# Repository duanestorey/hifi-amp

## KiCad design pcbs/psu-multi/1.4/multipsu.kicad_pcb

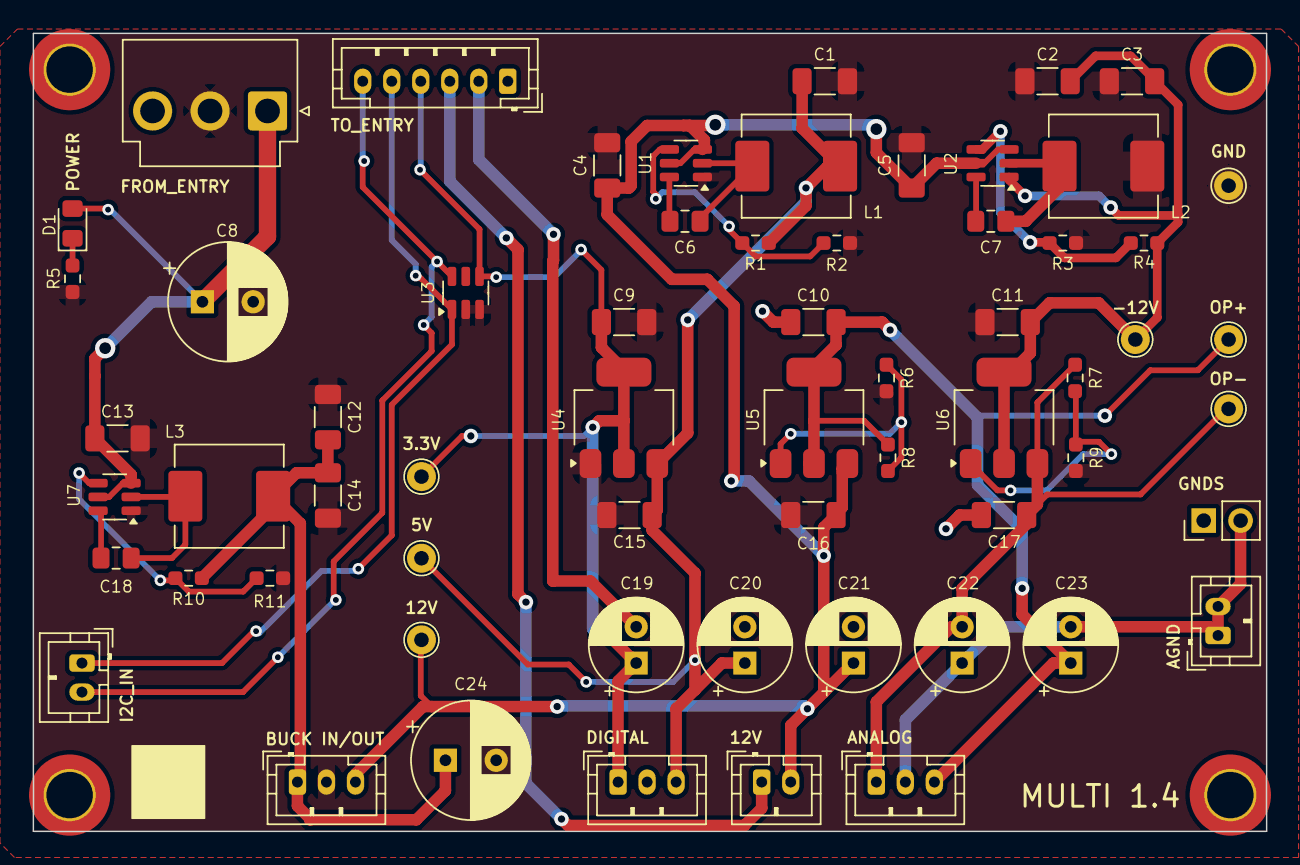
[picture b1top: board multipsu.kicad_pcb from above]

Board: 2 copper layers, 85.0 x 55.0 mm, 66 parts (0 on the bottom side), 27 nets.

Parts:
C1, C2, C3, C12, C14: 22U 25V; C_1206_3216Metric_Pad1.33x1.80mm_HandSolder
C4, C5, C13: 10U 50V; C_1206_3216Metric_Pad1.33x1.80mm_HandSolder
C6, C7, C18: 0.1u; C_0805_2012Metric_Pad1.18x1.45mm_HandSolder
C8: 100u 50V; CP_Radial_D8.0mm_P3.50mm
C9, C10, C15, C17: 10U; C_1206_3216Metric_Pad1.33x1.80mm_HandSolder
C11, C16: 10u; C_1206_3216Metric_Pad1.33x1.80mm_HandSolder
C19, C20, C21, C22, C23: 220u 16V; CP_Radial_D6.3mm_P2.50mm
C24: 1000u 16V; CP_Radial_D8.0mm_P3.50mm
D1: BLUE; LED_0805_2012Metric_Pad1.15x1.40mm_HandSolder
H1, H2, H3, H4: MountingHole; MountingHole_3.2mm_M3_DIN965_Pad_TopOnly
J1: Conn_01x06_Pin; JST_PH_B6B-PH-K_1x06_P2.00mm_Vertical
J2: Conn_01x03_Male; JST_VH_B3P-VH_1x03_P3.96mm_Vertical
J3: Conn_01x02; PinHeader_1x02_P2.54mm_Vertical
J4, J5, J8: Conn_01x02_Pin; JST_PH_B2B-PH-K_1x02_P2.00mm_Vertical
J6, J7, J9: Conn_01x03_Pin; JST_PH_B3B-PH-K_1x03_P2.00mm_Vertical
L1: 3.3u; L_Sunlord_MWSA0605S
L2, L3: 6.8u; L_Sunlord_MWSA0605S
R1, R3, R10: 100K; R_0603_1608Metric_Pad0.98x0.95mm_HandSolder
R2: 13.7K; R_0603_1608Metric_Pad0.98x0.95mm_HandSolder
R4, R11: 5.23K; R_0603_1608Metric_Pad0.98x0.95mm_HandSolder
R5: 16K; R_0603_1608Metric_Pad0.98x0.95mm_HandSolder
R6, R9: 1.6K; R_0603_1608Metric_Pad0.98x0.95mm_HandSolder
R7, R8: 240R; R_0603_1608Metric_Pad0.98x0.95mm_HandSolder
TP1, TP2, TP3, TP4, TP5, TP6, TP7: TestPoint; TestPoint_THTPad_D2.0mm_Drill1.0mm
U1, U2, U7: LMR51430; SOT-23-6
U3: TMP100; SOT-23-6
U4: ZLDO1117QG33TA; SOT-223-3_TabPin2
U5: LM317_SOT-223; SOT-223-3_TabPin2
U6: LM337_SOT223; SOT-223-3_TabPin2

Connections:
3V3: C9.1, C19.1, J1.4, J7.1, TP5.1, U3.4 (V+), U4.2 (VO)
5V: C1.1, C15.1, C20.1, J7.3, L1.2, R1.1, TP6.1, U4.3 (VI)
12V: C4.1, C5.1, C16.1, C21.1, J6.3, J8.2, TP7.1, U1.3 (VIN), U1.5 (EN), U2.3 (VIN), U2.5 (EN), U5.3 (VI)
12V_OUT: C12.1, C14.1, C24.1, J6.1, L3.2, R10.1
-12V: C2.2, C3.2, C11.2, R4.2, TP2.1, U2.1 (GND), U6.2 (VI)
AGND: C10.2, C17.1, J1.1, J3.1
AGND_INT: C22.1, C23.2, J3.2, J4.1, J4.2, J9.2
DC_NEG: C17.2, C22.2, J9.1, R7.1, TP4.1, U6.3 (VO)
DC_POS: C10.1, C23.1, J9.3, R8.1, TP3.1, U5.2 (VO)
GND: C19.2, C20.2, C21.2, J1.2, J7.2
unnamed: D1.1 (K), R5.1
unnamed: C6.1, U1.6 (CB)
unnamed: R1.2, R2.1, U1.4 (FB)
unnamed: C6.2, L1.1, U1.2 (SW)
unnamed: C7.1, U2.6 (CB)
unnamed: R3.2, R4.1, U2.4 (FB)
unnamed: C7.2, L2.1, U2.2 (SW)
unnamed: R6.1, R8.2, U5.1 (ADJ)
unnamed: R7.2, R9.1, U6.1 (ADJ)
unnamed: C18.1, U7.6 (CB)
unnamed: R10.2, R11.1, U7.4 (FB)
unnamed: C18.2, L3.1, U7.2 (SW)
PGND: C1.2, C2.1, C3.1, C4.2, C5.2, C8.2, C9.2, C11.1, C12.2, C13.2, C14.2, C15.2, C16.2, C24.2, J2.2, J6.2, L2.2, R2.2, R3.1, R5.2, R6.2, R9.2, R11.2, TP1.1, U1.1 (GND), U3.2 (GND), U3.3 (ADD1), U4.1 (GND), U7.1 (GND)
RELAY_GND: J1.3, J8.1
SCL: J1.5, J5.1, U3.1 (SCL)
SDA: J1.6, J5.2, U3.6 (SDA)
VP: C8.1, C13.1, D1.2 (A), J2.1, U7.3 (VIN), U7.5 (EN)

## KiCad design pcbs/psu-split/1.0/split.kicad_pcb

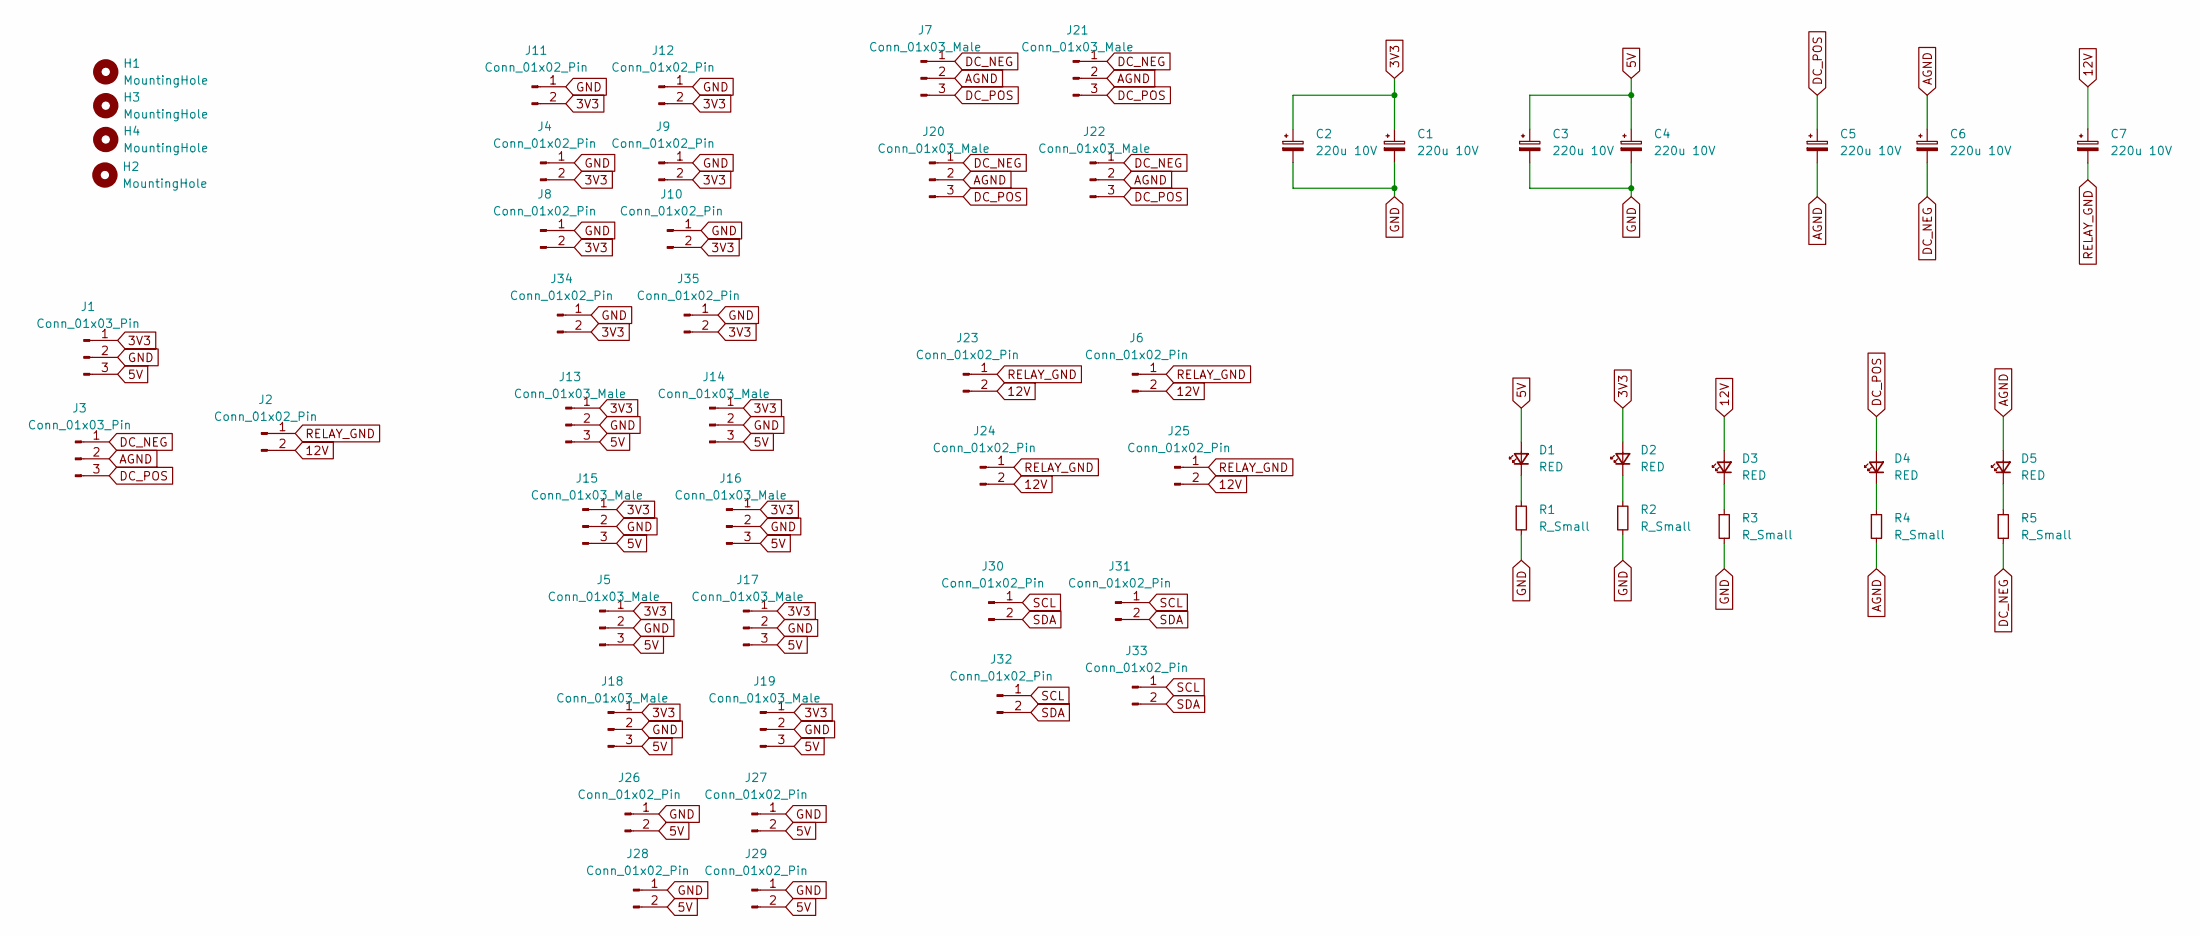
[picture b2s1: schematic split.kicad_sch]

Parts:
C1, C2, C3, C4, C5, C6: 220u 10V; CP_Radial_D10.0mm_P2.50mm_P5.00mm
C7: 220u 10V; CP_Radial_D6.3mm_P2.50mm
D1, D2, D3, D4, D5: RED; LED_0805_2012Metric_Pad1.15x1.40mm_HandSolder
H1, H2, H3, H4: MountingHole; MountingHole_3.2mm_M3_DIN965_Pad_TopOnly
J1, J3: Conn_01x03_Pin; JST_PH_B3B-PH-K_1x03_P2.00mm_Vertical
J2, J4, J6, J8, J9, J10, J11, J12, J23, J24, J25, J26, J27, J28, J29, J30, J31, J32, J33, J34, J35: Conn_01x02_Pin; JST_PH_B2B-PH-K_1x02_P2.00mm_Vertical
J5, J7, J13, J14, J15, J16, J17, J18, J19, J20, J21, J22: Conn_01x03_Male; JST_PH_B3B-PH-K_1x03_P2.00mm_Vertical
R1, R2, R3, R4, R5: R_Small; R_0603_1608Metric_Pad0.98x0.95mm_HandSolder

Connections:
3V3: C1.1, C2.1, D2.2 (A), J1.1, J4.2, J5.1, J8.2, J9.2, J10.2, J11.2, J12.2, J13.1, J14.1, J15.1, J16.1, J17.1, J18.1, J19.1, J34.2, J35.2
5V: C3.1, C4.1, D1.2 (A), J1.3, J5.3, J13.3, J14.3, J15.3, J16.3, J17.3, J18.3, J19.3, J26.2, J27.2, J28.2, J29.2
12V: C7.1, D3.2 (A), J2.2, J6.2, J23.2, J24.2, J25.2
AGND: C5.2, C6.1, D5.2 (A), J3.2, J7.2, J20.2, J21.2, J22.2, R4.2
DC_NEG: C6.2, J3.1, J7.1, J20.1, J21.1, J22.1, R5.2
DC_POS: C5.1, D4.2 (A), J3.3, J7.3, J20.3, J21.3, J22.3
GND: C1.2, C2.2, C3.2, C4.2, J1.2, J4.1, J5.2, J8.1, J9.1, J10.1, J11.1, J12.1, J13.2, J14.2, J15.2, J16.2, J17.2, J18.2, J19.2, J26.1, J27.1, J28.1, J29.1, J34.1, J35.1, R1.2, R2.2, R3.2
unnamed: D1.1 (K), R1.1
unnamed: D2.1 (K), R2.1
unnamed: D3.1 (K), R3.1
unnamed: D4.1 (K), R4.1
unnamed: D5.1 (K), R5.1
RELAY_GND: C7.2, J2.1, J6.1, J23.1, J24.1, J25.1
SCL: J30.1, J31.1, J32.1, J33.1
SDA: J30.2, J31.2, J32.2, J33.2

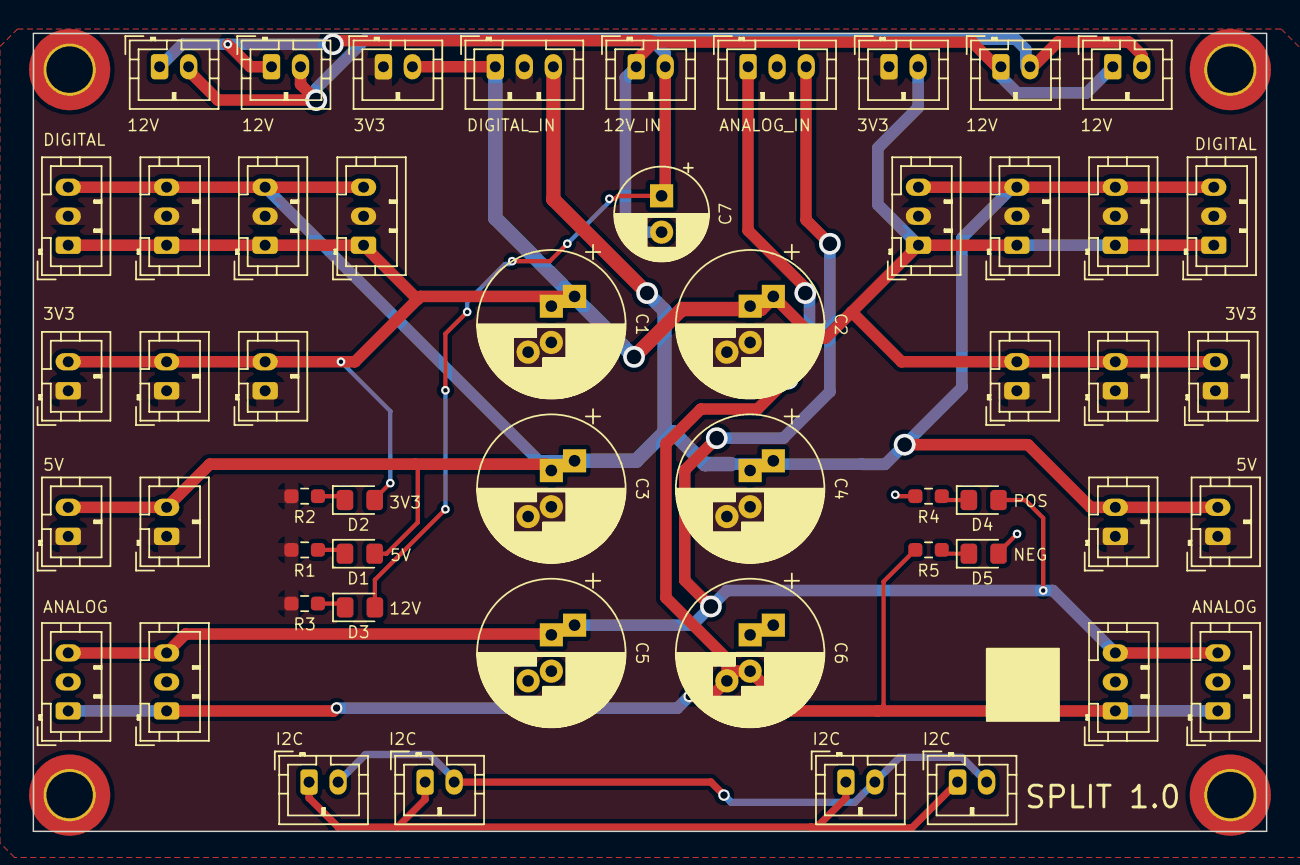
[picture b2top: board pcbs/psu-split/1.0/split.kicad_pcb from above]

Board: 2 copper layers, 85.0 x 55.0 mm, 56 parts (0 on the bottom side), 15 nets.

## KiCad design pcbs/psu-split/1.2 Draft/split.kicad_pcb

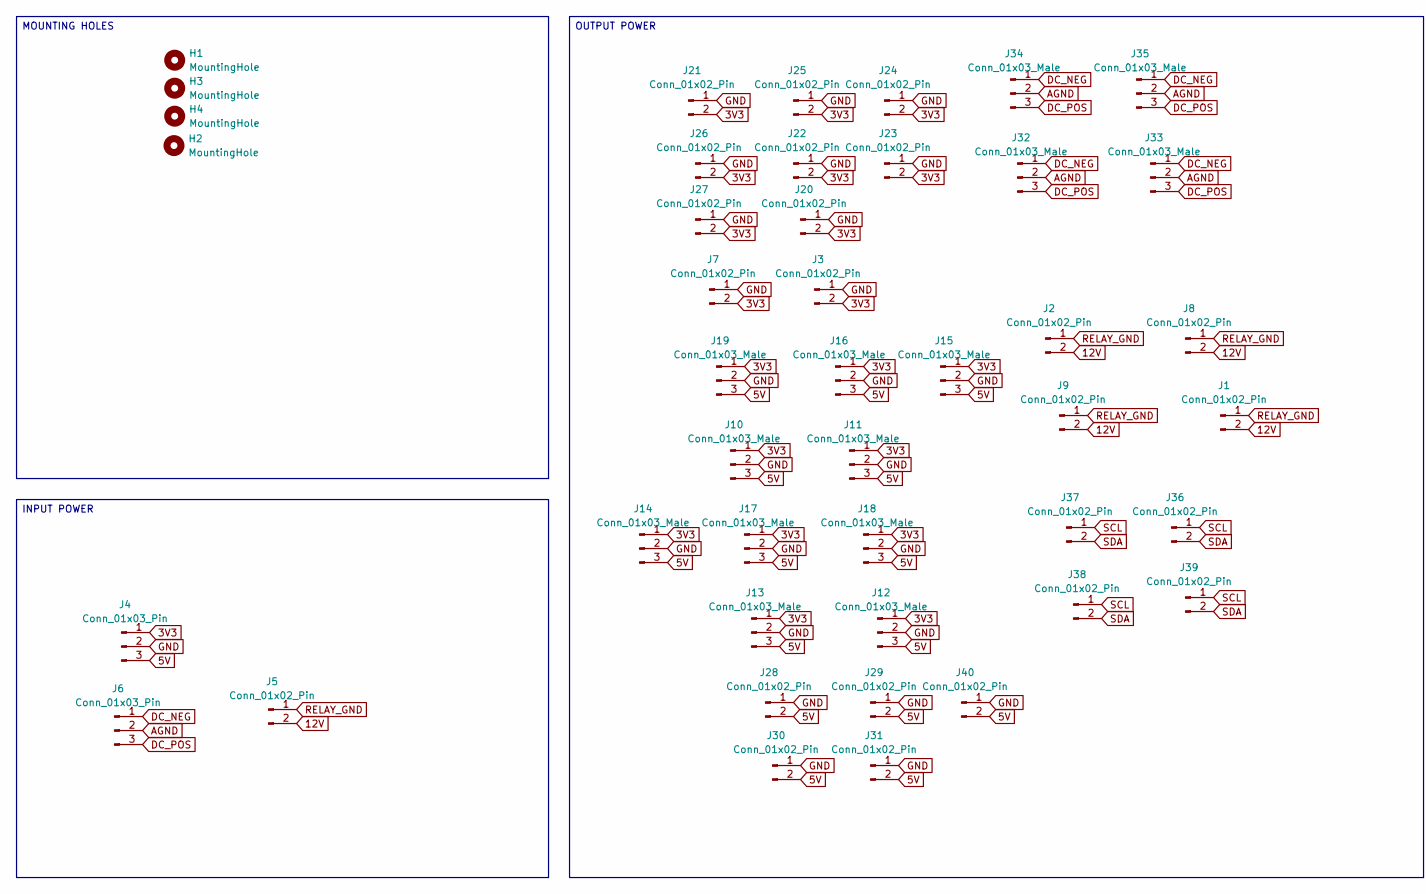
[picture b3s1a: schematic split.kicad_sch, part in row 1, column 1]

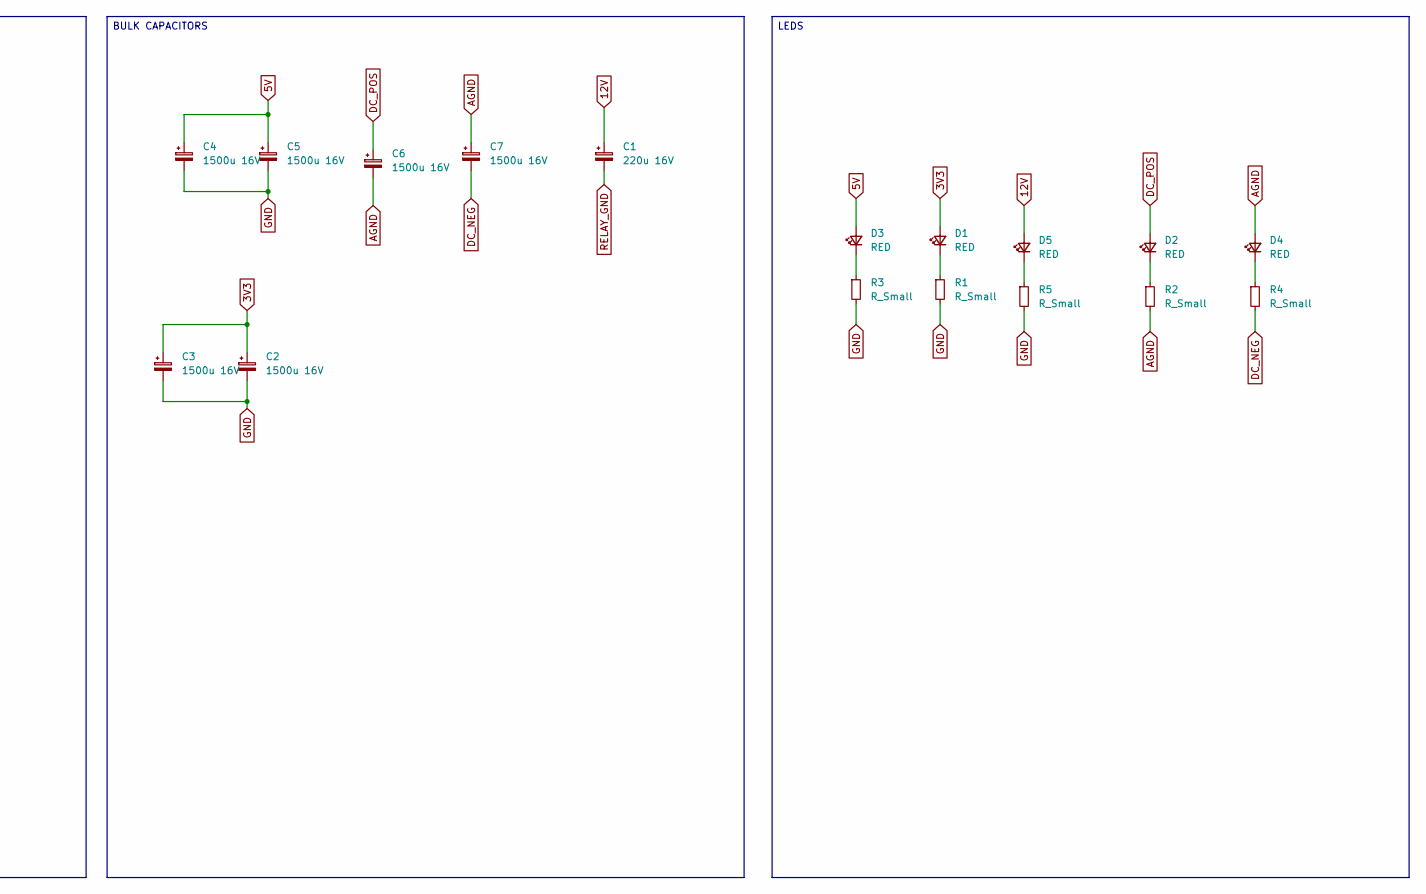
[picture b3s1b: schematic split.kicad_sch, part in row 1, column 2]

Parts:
C1: 220u 16V; CP_Radial_D6.3mm_P2.50mm
C2, C3, C4, C5, C6, C7: 1500u 16V; CP_Radial_D10.0mm_P2.50mm_P5.00mm
D1, D2, D3, D4, D5: RED; LED_0805_2012Metric_Pad1.15x1.40mm_HandSolder
H1, H2, H3, H4: MountingHole; MountingHole_3.2mm_M3_DIN965_Pad_TopOnly
J1, J2, J3, J5, J7, J8, J9, J20, J21, J22, J23, J24, J25, J26, J27, J28, J29, J30, J31, J36, J37, J38, J39, J40: Conn_01x02_Pin; JST_PH_B2B-PH-K_1x02_P2.00mm_Vertical
J4, J6: Conn_01x03_Pin; JST_PH_B3B-PH-K_1x03_P2.00mm_Vertical
J10, J11, J12, J13, J14, J15, J16, J17, J18, J19, J32, J33, J34, J35: Conn_01x03_Male; JST_PH_B3B-PH-K_1x03_P2.00mm_Vertical
R1, R2, R3, R4, R5: R_Small; R_0603_1608Metric_Pad0.98x0.95mm_HandSolder

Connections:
3V3: C2.1, C3.1, D1.2 (A), J3.2, J4.1, J7.2, J10.1, J11.1, J12.1, J13.1, J14.1, J15.1, J16.1, J17.1, J18.1, J19.1, J20.2, J21.2, J22.2, J23.2, J24.2, J25.2, J26.2, J27.2
5V: C4.1, C5.1, D3.2 (A), J4.3, J10.3, J11.3, J12.3, J13.3, J14.3, J15.3, J16.3, J17.3, J18.3, J19.3, J28.2, J29.2, J30.2, J31.2, J40.2
12V: C1.1, D5.2 (A), J1.2, J2.2, J5.2, J8.2, J9.2
AGND: C6.2, C7.1, D4.2 (A), J6.2, J32.2, J33.2, J34.2, J35.2, R2.2
DC_NEG: C7.2, J6.1, J32.1, J33.1, J34.1, J35.1, R4.2
DC_POS: C6.1, D2.2 (A), J6.3, J32.3, J33.3, J34.3, J35.3
GND: C2.2, C3.2, C4.2, C5.2, J3.1, J4.2, J7.1, J10.2, J11.2, J12.2, J13.2, J14.2, J15.2, J16.2, J17.2, J18.2, J19.2, J20.1, J21.1, J22.1, J23.1, J24.1, J25.1, J26.1, J27.1, J28.1, J29.1, J30.1, J31.1, J40.1, R1.2, R3.2, R5.2
unnamed: D1.1 (K), R1.1
unnamed: D2.1 (K), R2.1
unnamed: D3.1 (K), R3.1
unnamed: D4.1 (K), R4.1
unnamed: D5.1 (K), R5.1
RELAY_GND: C1.2, J1.1, J2.1, J5.1, J8.1, J9.1
SCL: J36.1, J37.1, J38.1, J39.1
SDA: J36.2, J37.2, J38.2, J39.2

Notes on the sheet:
LEDS
MOUNTING HOLES
INPUT POWER
OUTPUT POWER
BULK CAPACITORS

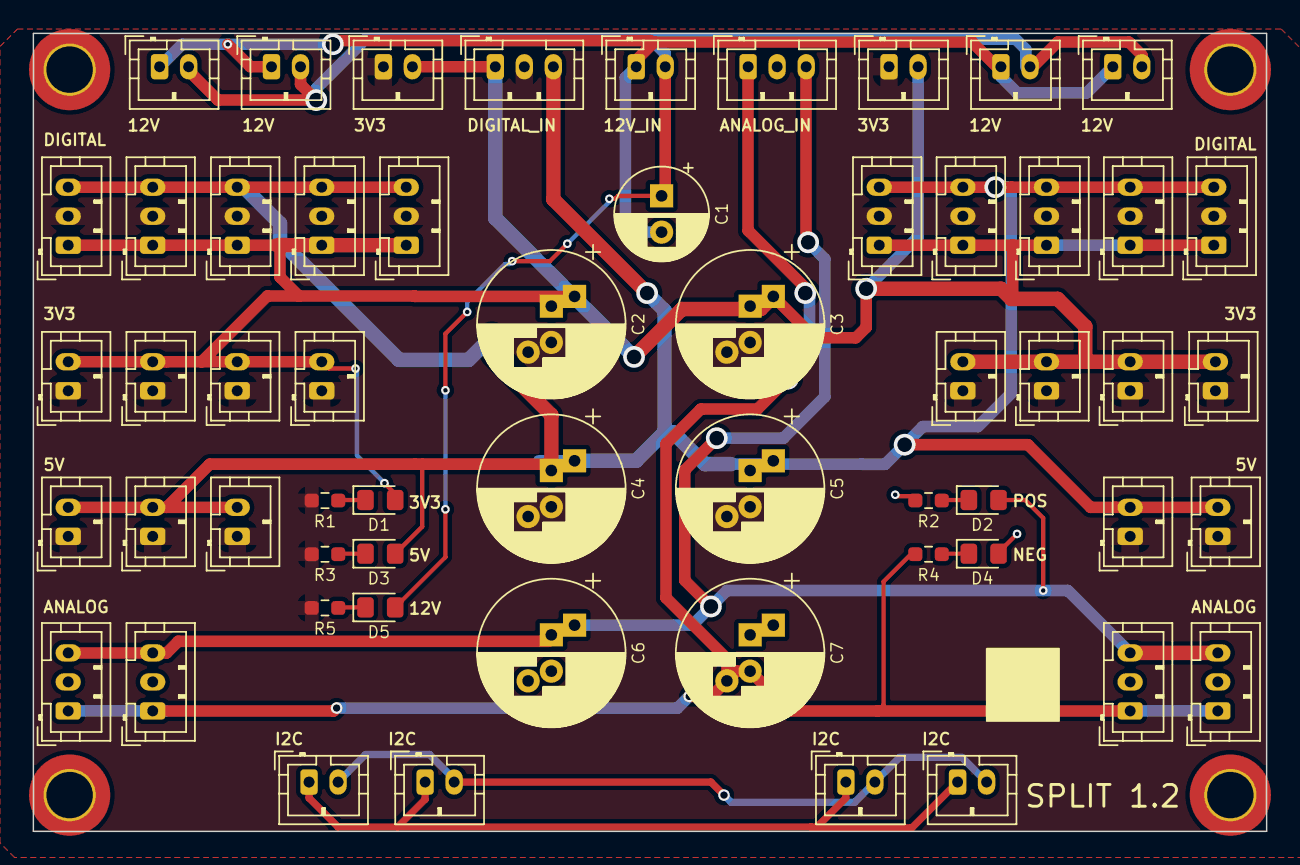
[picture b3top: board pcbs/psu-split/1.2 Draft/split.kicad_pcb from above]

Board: 2 copper layers, 85.0 x 55.0 mm, 61 parts (0 on the bottom side), 15 nets.

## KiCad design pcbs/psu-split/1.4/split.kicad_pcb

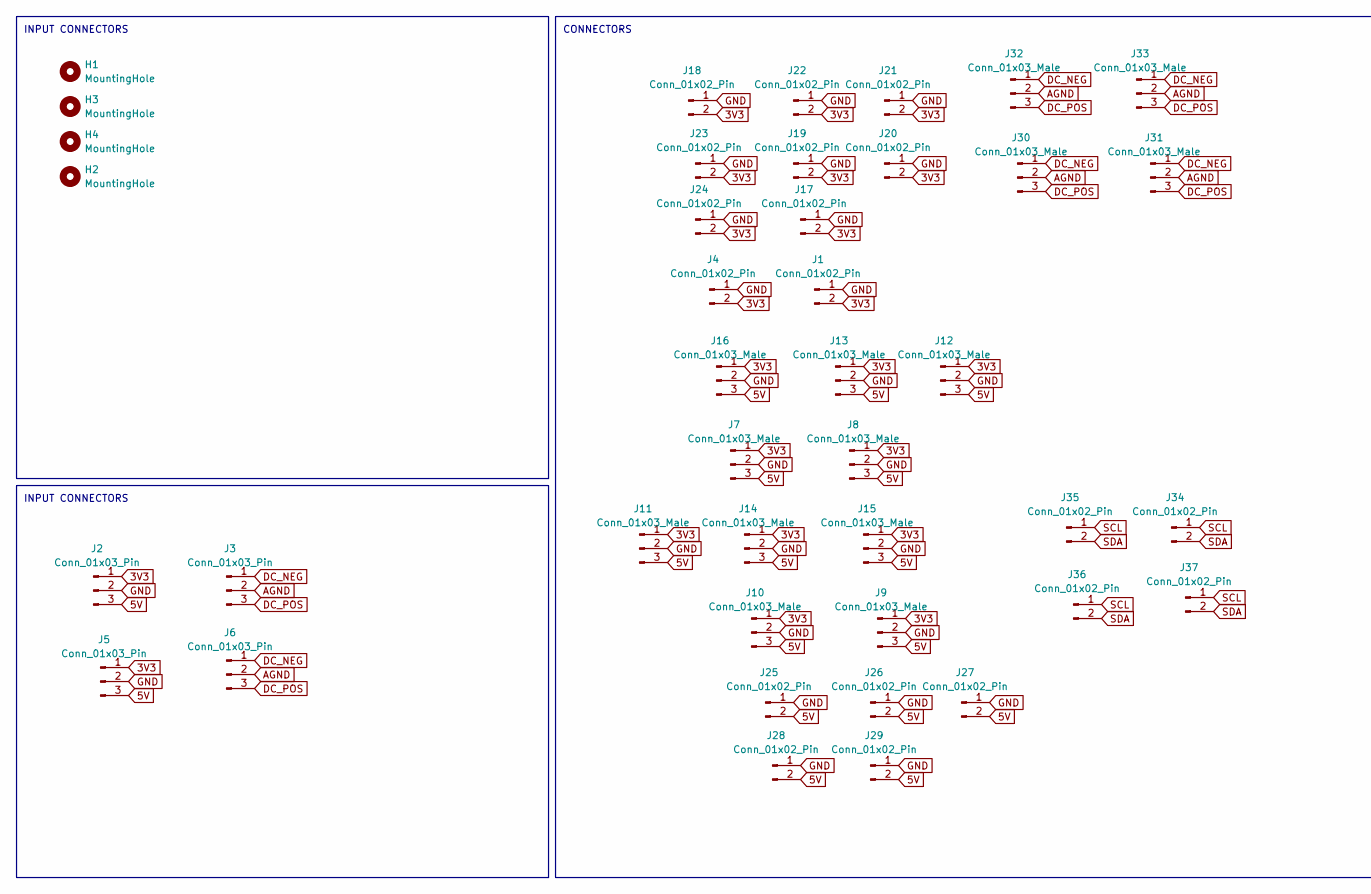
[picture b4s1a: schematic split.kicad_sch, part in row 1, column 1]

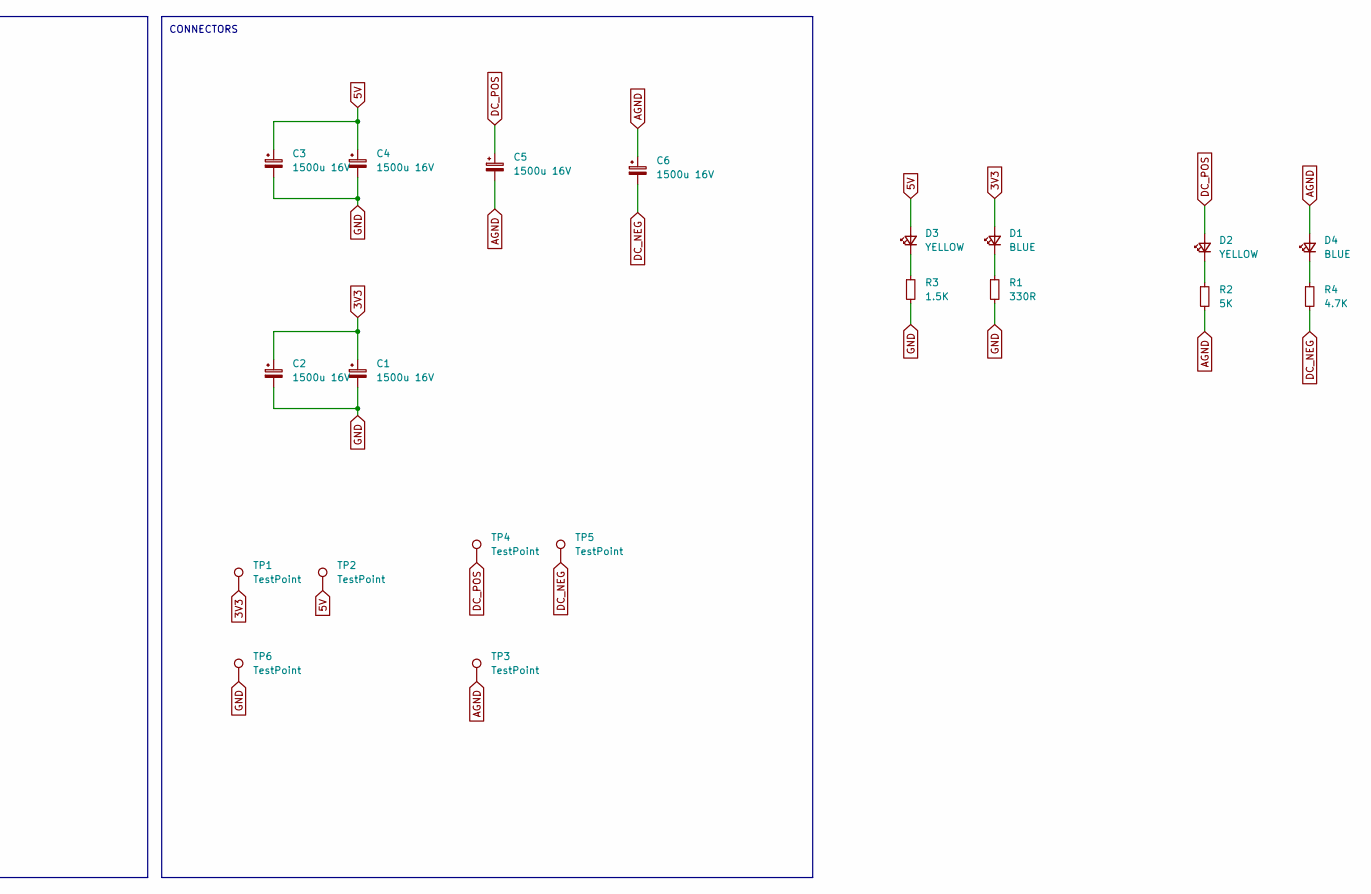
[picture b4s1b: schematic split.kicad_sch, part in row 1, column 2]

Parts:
C1, C2, C3, C4, C5, C6: 1500u 16V; CP_Radial_D10.0mm_P2.50mm_P5.00mm
D1, D4: BLUE; LED_0805_2012Metric_Pad1.15x1.40mm_HandSolder
D2, D3: YELLOW; LED_0805_2012Metric_Pad1.15x1.40mm_HandSolder
H1, H2, H3, H4: MountingHole; MountingHole_3.2mm_M3_DIN965_Pad_TopOnly
J1, J4, J17, J18, J19, J20, J21, J22, J23, J24, J25, J26, J27, J28, J29, J34, J35, J36, J37: Conn_01x02_Pin; JST_PH_B2B-PH-K_1x02_P2.00mm_Vertical
J2, J3: Conn_01x03_Pin; JST_PH_B3B-PH-K_1x03_P2.00mm_Vertical
J5, J6: Conn_01x03_Pin; TerminalBlock_Phoenix_PT-1,5-3-3.5-H_1x03_P3.50mm_Horizontal
J7, J8, J9, J10, J11, J12, J13, J14, J15, J16, J30, J31, J32, J33: Conn_01x03_Male; JST_PH_B3B-PH-K_1x03_P2.00mm_Vertical
R1: 330R; R_0805_2012Metric_Pad1.20x1.40mm_HandSolder
R2: 5K; R_0805_2012Metric_Pad1.20x1.40mm_HandSolder
R3: 1.5K; R_0805_2012Metric_Pad1.20x1.40mm_HandSolder
R4: 4.7K; R_0805_2012Metric_Pad1.20x1.40mm_HandSolder
TP1, TP2, TP3, TP4, TP5, TP6: TestPoint; TestPoint_THTPad_2.5x2.5mm_Drill1.2mm

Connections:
3V3: C1.1, C2.1, D1.2 (A), J1.2, J2.1, J4.2, J5.1, J7.1, J8.1, J9.1, J10.1, J11.1, J12.1, J13.1, J14.1, J15.1, J16.1, J17.2, J18.2, J19.2, J20.2, J21.2, J22.2, J23.2, J24.2, TP1.1
5V: C3.1, C4.1, D3.2 (A), J2.3, J5.3, J7.3, J8.3, J9.3, J10.3, J11.3, J12.3, J13.3, J14.3, J15.3, J16.3, J25.2, J26.2, J27.2, J28.2, J29.2, TP2.1
AGND: C5.2, C6.1, D4.2 (A), J3.2, J6.2, J30.2, J31.2, J32.2, J33.2, R2.2, TP3.1
DC_NEG: C6.2, J3.1, J6.1, J30.1, J31.1, J32.1, J33.1, R4.2, TP5.1
DC_POS: C5.1, D2.2 (A), J3.3, J6.3, J30.3, J31.3, J32.3, J33.3, TP4.1
GND: C1.2, C2.2, C3.2, C4.2, J1.1, J2.2, J4.1, J5.2, J7.2, J8.2, J9.2, J10.2, J11.2, J12.2, J13.2, J14.2, J15.2, J16.2, J17.1, J18.1, J19.1, J20.1, J21.1, J22.1, J23.1, J24.1, J25.1, J26.1, J27.1, J28.1, J29.1, R1.2, R3.2, TP6.1
unnamed: D1.1 (K), R1.1
unnamed: D2.1 (K), R2.1
unnamed: D3.1 (K), R3.1
unnamed: D4.1 (K), R4.1
SCL: J34.1, J35.1, J36.1, J37.1
SDA: J34.2, J35.2, J36.2, J37.2

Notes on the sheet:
CONNECTORS
INPUT CONNECTORS

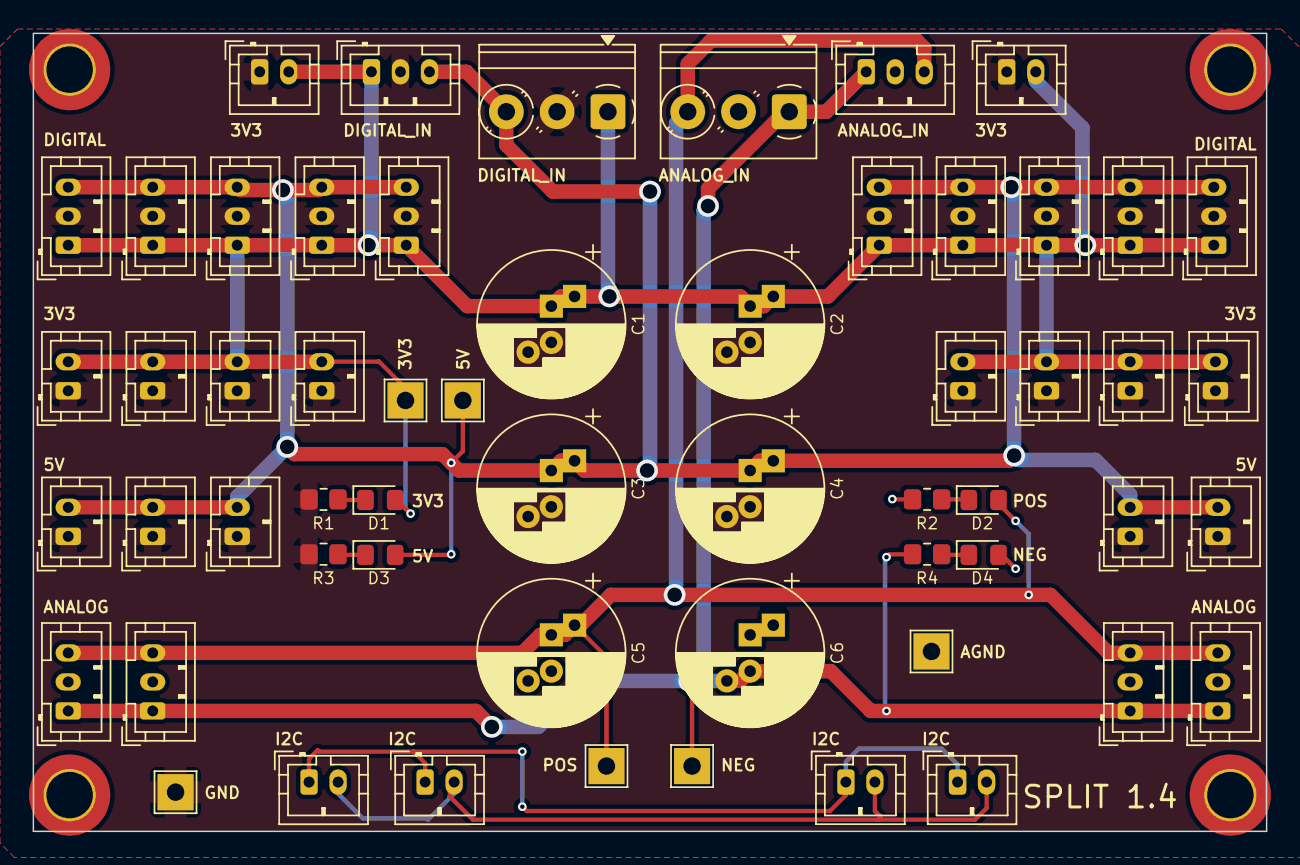
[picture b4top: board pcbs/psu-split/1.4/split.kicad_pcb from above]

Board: 2 copper layers, 85.0 x 55.0 mm, 61 parts (0 on the bottom side), 12 nets.

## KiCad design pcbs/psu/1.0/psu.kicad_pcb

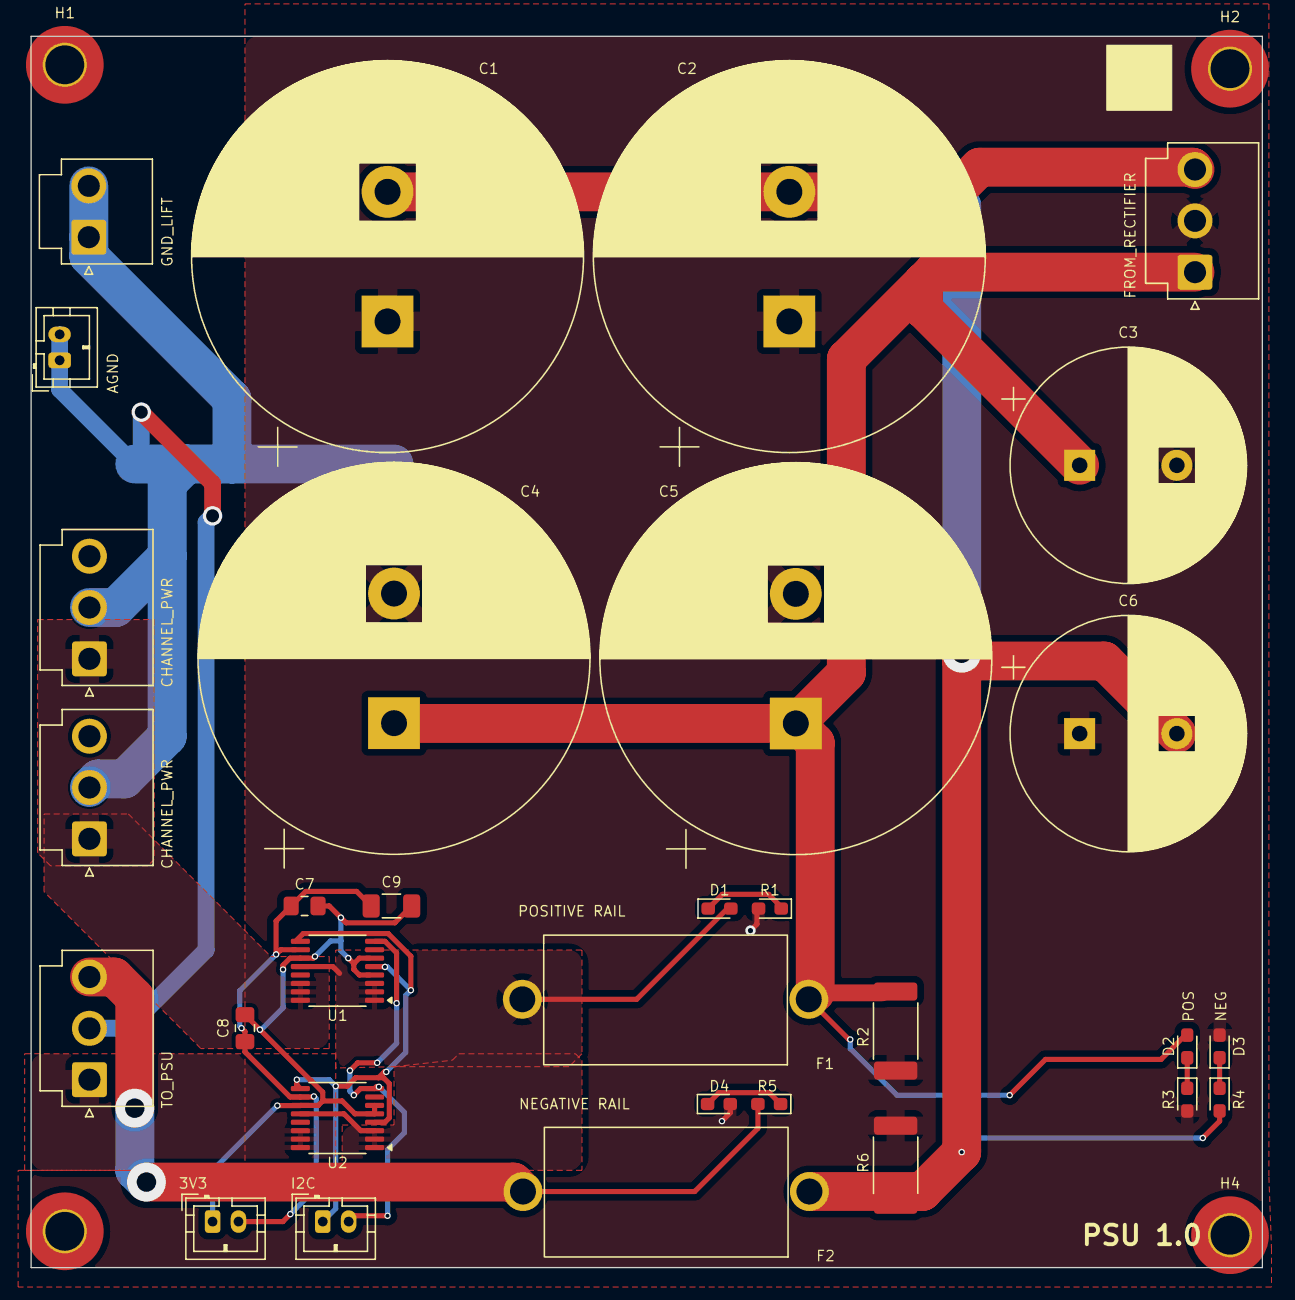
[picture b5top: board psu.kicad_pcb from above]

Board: 2 copper layers, 95.0 x 95.0 mm, 35 parts (0 on the bottom side), 15 nets.

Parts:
C1, C2, C4, C5: 15000U; CP_Radial_D30.0mm_P10.00mm_SnapIn
C3, C6: 3300u 50V; CP_Radial_D18.0mm_P7.50mm
C7, C8: 0.1u; C_0805_2012Metric_Pad1.18x1.45mm_HandSolder
C9: 10u; C_1206_3216Metric_Pad1.33x1.80mm_HandSolder
D1, D2: YELLOW; LED_0603_1608Metric_Pad1.05x0.95mm_HandSolder
D3, D4: BLUE; LED_0603_1608Metric_Pad1.05x0.95mm_HandSolder
F1, F2: Fuse_Small; Aliexpress Fuse 5x20
H1, H2, H3, H4: MountingHole; MountingHole_3mm_Pad_TopOnly
J1: Conn_01x02_Male; JST_VH_B2P-VH-B_1x02_P3.96mm_Vertical
J2, J4, J5, J6: Conn_01x03_Male; JST_VH_B3P-VH_1x03_P3.96mm_Vertical
J3, J7: Conn_01x02_Pin; JST_PH_B2B-PH-K_1x02_P2.00mm_Vertical
J8: Conn_01x02_Male; JST_PH_B2B-PH-K_1x02_P2.00mm_Vertical
R1, R3, R4, R5: 16K; LED_0603_1608Metric_Pad1.05x0.95mm_HandSolder
R2, R6: 1.5K 2W; R_2512_6332Metric_Pad1.40x3.35mm_HandSolder
U1, U2: INA260; TSSOP-16_4.4x5mm_P0.65mm

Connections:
3V3: C7.1, C8.1, C9.1, J7.2, U1.10 (VS), U2.10 (VS)
GND: C7.2, C8.2, C9.2, J7.1, U1.4 (A1), U1.6 (GND), U1.11 (GND), U2.5 (A0), U2.6 (GND), U2.11 (GND)
unnamed: D1.1 (K), R1.1
unnamed: D2.1 (K), R3.1
unnamed: D3.1 (K), R4.1
unnamed: D4.1 (K), R5.1
PGND: C1.1, C2.1, C3.2, C4.2, C5.2, C6.1, D3.2 (A), D4.2 (A), J1.1, J1.2, J2.2, J3.1, J3.2, J4.2, J5.2, J6.2, R1.2, R2.2, R3.2, R6.1
SCL: J8.1, U1.5 (A0), U1.9 (SCL), U2.4 (A1), U2.9 (SCL)
SDA: J8.2, U1.8 (SDA), U2.8 (SDA)
VM1: C1.2, C2.2, C6.2, F2.1, J2.3, R4.2, R6.2
VNOUT: F2.2, J4.3, J5.3, J6.3, R5.2
VP1: C3.1, C4.1, C5.1, D2.2 (A), F1.1, J2.1, R2.1
VPOUT: D1.2 (A), F1.2, U1.1 (IN+), U1.2 (IN+), U1.3 (IN+), U1.12 (VBUS), U2.1 (IN+), U2.2 (IN+), U2.3 (IN+), U2.12 (VBUS)
VPOUT_CHAN: J4.1, J5.1, U1.14 (IN-), U1.15 (IN-), U1.16 (IN-)
VPOUT_PSU: J6.1, U2.14 (IN-), U2.15 (IN-), U2.16 (IN-)

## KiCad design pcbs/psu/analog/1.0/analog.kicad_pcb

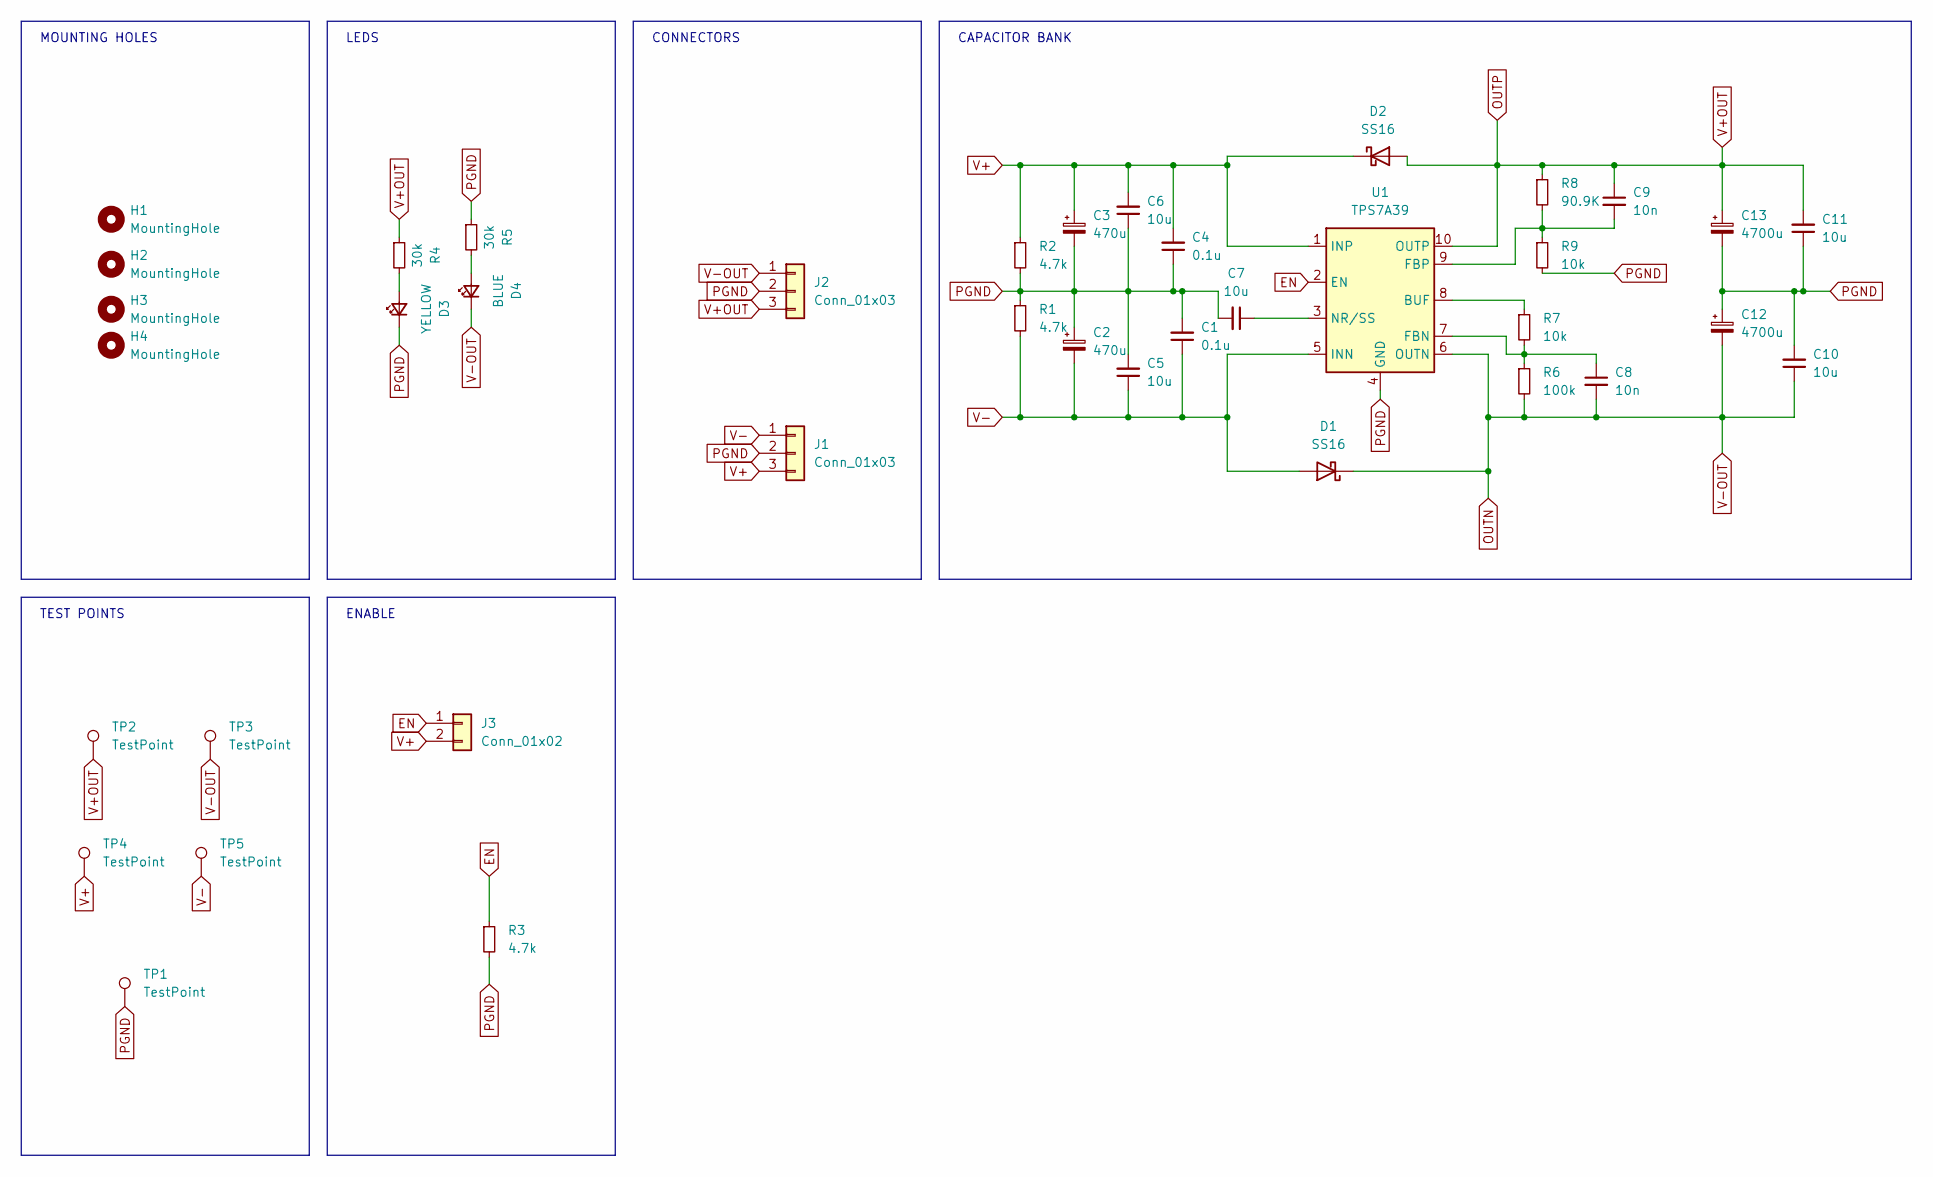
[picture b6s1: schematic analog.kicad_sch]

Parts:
C1, C4: 0.1u; C_0805_2012Metric_Pad1.18x1.45mm_HandSolder
C2, C3: 470u; CP_Radial_D8.0mm_P5.00mm
C5, C6, C7, C10, C11: 10u; C_1206_3216Metric_Pad1.33x1.80mm_HandSolder
C8, C9: 10n; C_0805_2012Metric_Pad1.18x1.45mm_HandSolder
C12, C13: 4700u; CP_Radial_D16.0mm_P7.50mm
D1, D2: SS16; D_SMA
D3: YELLOW; LED_0805_2012Metric_Pad1.15x1.40mm_HandSolder
D4: BLUE; LED_0805_2012Metric_Pad1.15x1.40mm_HandSolder
H1, H2, H3, H4: MountingHole; MountingHole_3.2mm_M3_DIN965_Pad_TopBottom
J1, J2: Conn_01x03; JST_VH_B3P-VH-B_1x03_P3.96mm_Vertical
J3: Conn_01x02; PinHeader_1x02_P2.54mm_Vertical
R1, R2, R3: 4.7k; R_0805_2012Metric_Pad1.20x1.40mm_HandSolder
R4, R5: 30k; R_0805_2012Metric_Pad1.20x1.40mm_HandSolder
R6: 100k; R_0805_2012Metric_Pad1.20x1.40mm_HandSolder
R7, R9: 10k; R_0805_2012Metric_Pad1.20x1.40mm_HandSolder
R8: 90.9K; R_0805_2012Metric_Pad1.20x1.40mm_HandSolder
TP1, TP2, TP3, TP4, TP5: TestPoint; TestPoint_THTPad_2.5x2.5mm_Drill1.2mm
U1: TPS7A39; Texas_S-PVSON-N10_ThermalVias

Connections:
EN: J3.1, R3.1, U1.2 (EN)
unnamed: D3.2 (A), R4.2
unnamed: D4.2 (A), R5.2
unnamed: R7.1, U1.8 (BUF)
unnamed: C8.1, R6.1, R7.2, U1.7 (FBN)
unnamed: C9.2, R8.2, R9.1, U1.9 (FBP)
unnamed: C7.1, U1.3 (NR/SS)
OUTN: C8.2, C10.1, C12.2, D1.1 (K), D4.1 (K), J2.1, R6.2, TP3.1, U1.6 (OUTN)
OUTP: C9.1, C11.2, C13.1, D2.2 (A), J2.3, R4.1, R8.1, TP2.1, U1.10 (OUTP)
PGND: C1.2, C2.1, C3.2, C4.1, C5.2, C6.1, C7.2, C10.2, C11.1, C12.1, C13.2, D3.1 (K), J1.2, J2.2, R1.1, R2.2, R3.2, R5.1, R9.2, TP1.1, U1.4 (GND), U1.11 (GND)
V+: C3.1, C4.2, C6.2, D2.1 (K), J1.3, J3.2, R2.1, TP4.1, U1.1 (INP)
V-: C1.1, C2.2, C5.1, D1.2 (A), J1.1, R1.2, TP5.1, U1.5 (INN)

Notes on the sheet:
CAPACITOR BANK
MOUNTING HOLES
LEDS
CONNECTORS
TEST POINTS
ENABLE
